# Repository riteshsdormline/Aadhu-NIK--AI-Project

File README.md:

# Aadhu-NIK--AI-Project
1. Schematic and PCB Design
   consisting of Scheamtic Diagram and PCB Design for used components(Designed on KiCAD)

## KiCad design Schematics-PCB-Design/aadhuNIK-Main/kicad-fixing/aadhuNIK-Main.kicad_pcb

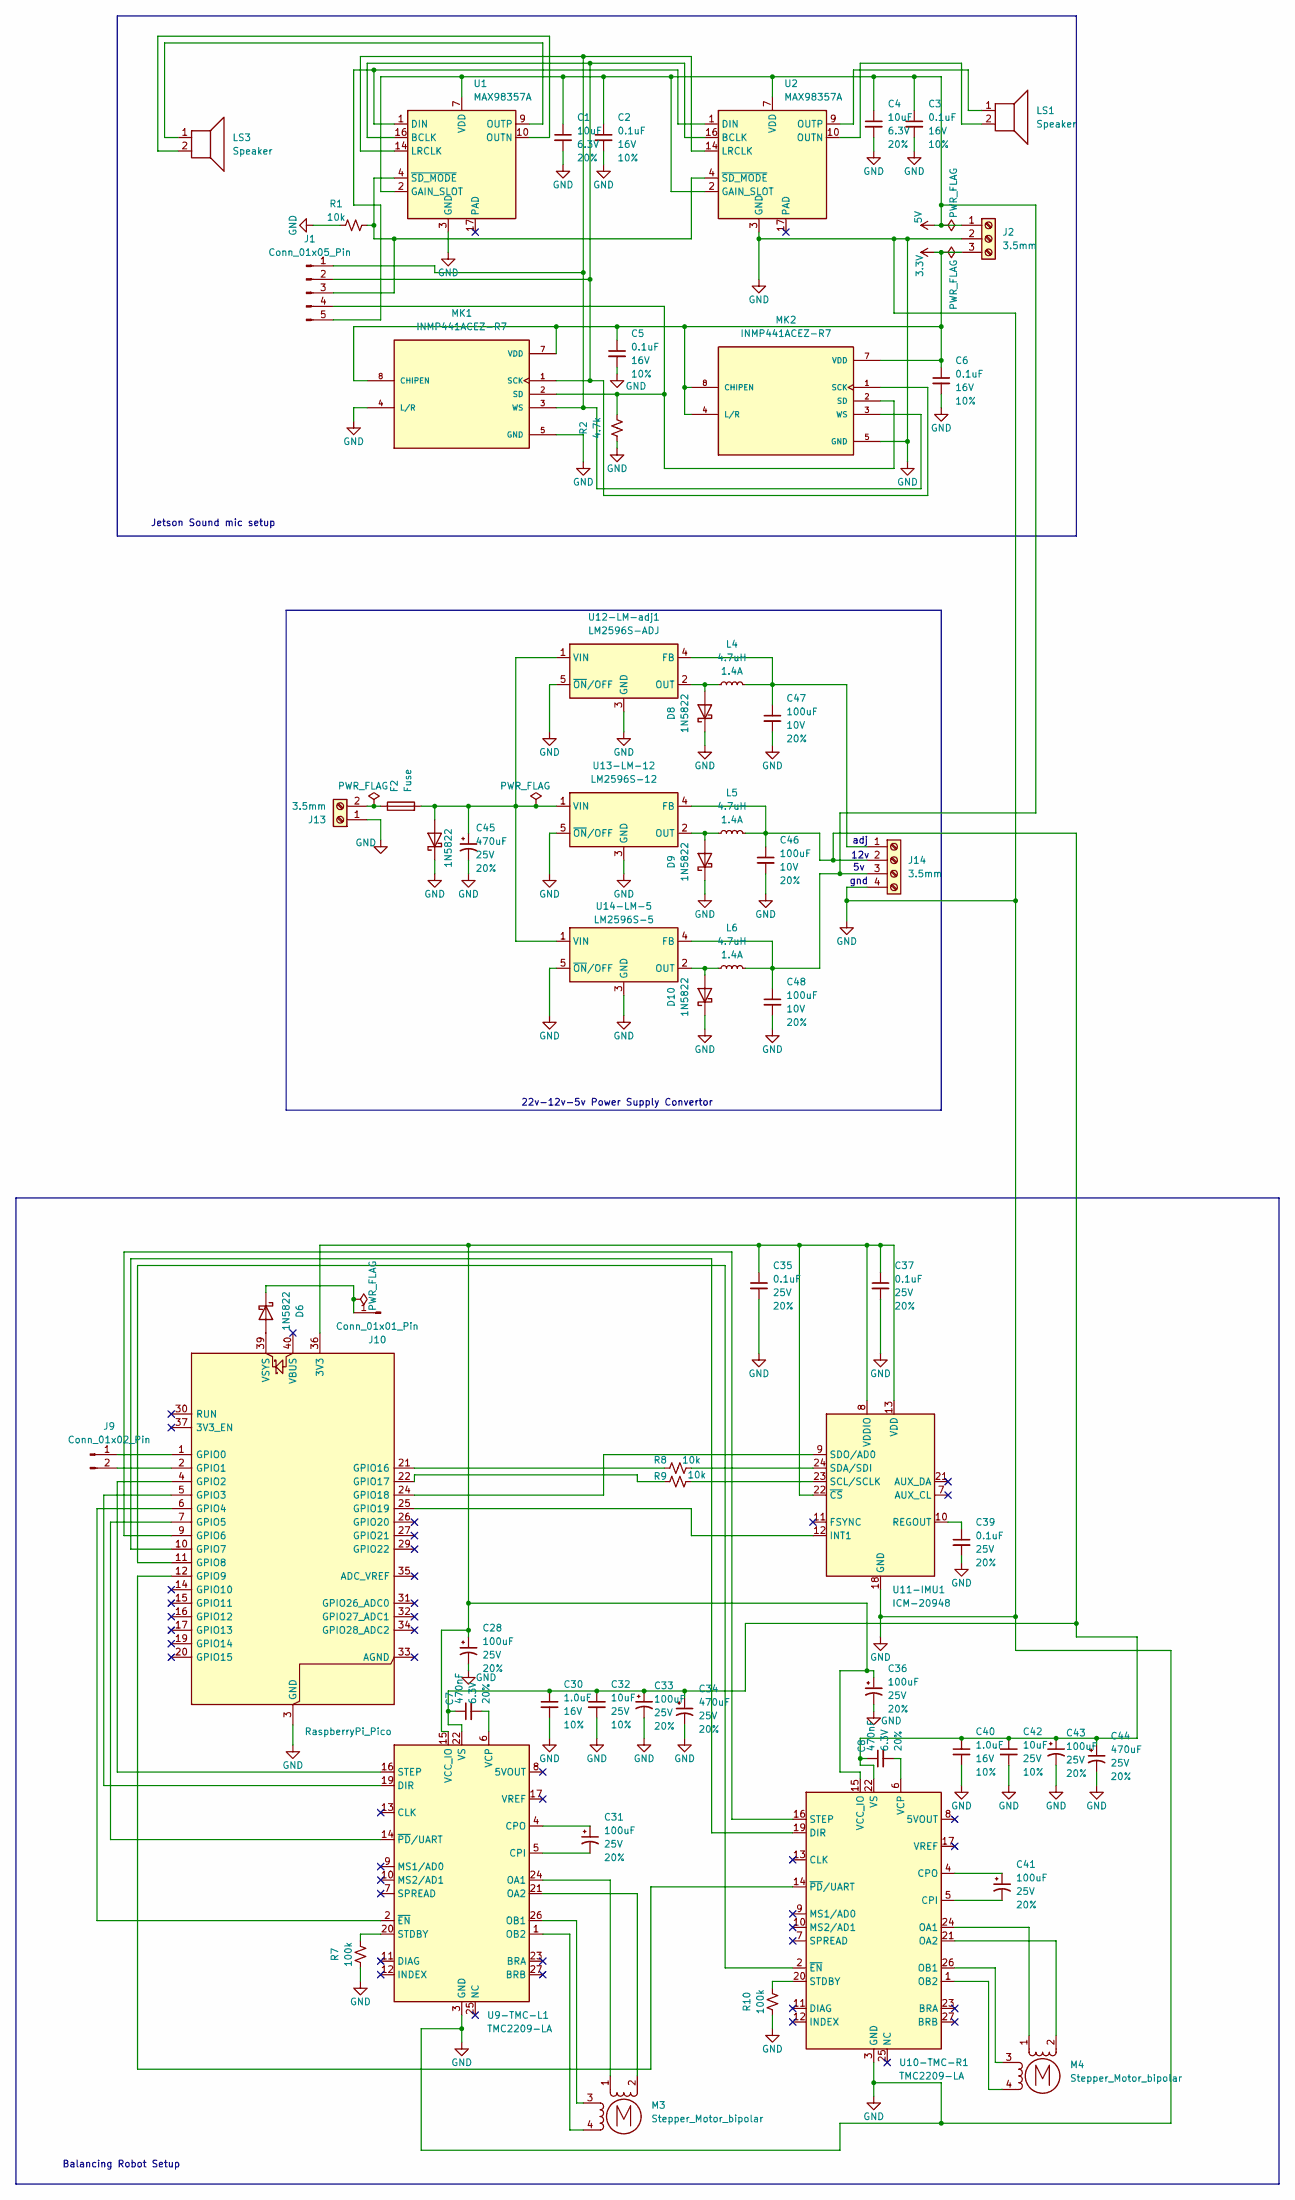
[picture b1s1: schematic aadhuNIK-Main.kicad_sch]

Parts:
A2: RaspberryPi_Pico; RaspberryPi_Pico_Common_Unspecified
C1, C4: 10uF; C_0402_1005Metric; Voltage 6.3V; Tolerance 20%
C2: 0.1uF; C_01005_0402Metric; Voltage 16V; Tolerance 10%
C3, C5, C6: 0.1uF; C_0402_1005Metric; Voltage 16V; Tolerance 10%
C7, C8: 470nF; C_0201_0603Metric; Voltage 6.3V; Tolerance 20%
C28, C31, C33, C36, C41, C43: 100uF; Panasonic_D; Voltage 25V; Tolerance 20%
C30, C40: 1.0uF; C_0402_1005Metric; Voltage 16V; Tolerance 10%
C32, C42: 10uF; C_0805_2012Metric; Voltage 25V; Tolerance 10%
C34, C44, C45: 470uF; Electrolytic_10.3x10.3mm; Voltage 25V; Tolerance 20%
C35, C37, C39: 0.1uF; C_0603_1608Metric; Voltage 25V; Tolerance 20%
C46, C47, C48: 100uF; C_1206_3216Metric; Voltage 10V; Tolerance 20%
D6, D7, D8, D9, D10: 1N5822; D_DO-201AD_P15.24mm_Horizontal
F2: Fuse; Fuse_0603_1608Metric
J1: Conn_01x05_Pin; Hirose_DF13-05P-1.25DSA_1x05_P1.25mm_Vertical
J2: 3.5mm; ScrewTerminal_1x03_P3.5mm_Horizontal_Black
J9: Conn_01x02_Pin; JWT_A3963_1x02_P3.96mm_Vertical
J10: Conn_01x01_Pin; Hirose_DF63M-1P-3.96DSA_1x01_P3.96mm_Vertical
J13: 3.5mm; ScrewTerminal_1x02_P3.5mm_Horizontal_Black
J14: 3.5mm; ScrewTerminal_1x04_P3.5mm_Horizontal
L4, L5, L6: 4.7uH; 1008_2520Metric
LS1, LS3: Speaker; JWT_A3963_1x02_P3.96mm_Vertical
M3, M4: Stepper_Motor_bipolar; PinHeader_1x04_P2.54mm_Vertical
MK1, MK2: INMP441ACEZ-R7; MIC_INMP441ACEZ-R7; PARTREV 1.1
R1: 10k; R_0402_1005Metric
R2: 4.7k; R_0402_1005Metric
R7, R10: 100k; R_0603_1608Metric
R8, R9: 10k; R_0603_1608Metric
U1: MAX98357A; TQFN-16-1EP_3x3mm_P0.5mm_EP1.23x1.23mm_ThermalVias
U2: MAX98357A; TQFN-16-1EP_3x3mm_P0.5mm_EP1.23x1.23mm
U9-TMC-L1, U10-TMC-R1: TMC2209-LA; VQFN-28-1EP_5x5mm_P0.5mm_EP3.7x3.7mm_ThermalVias
U11-IMU1: ICM-20948; InvenSense_QFN-24_3x3mm_P0.4mm
U12-LM-adj1: LM2596S-ADJ; TO-263-5_TabPin3
U13-LM-12: LM2596S-12; TO-263-5_TabPin3
U14-LM-5: LM2596S-5; TO-263-5_TabPin3

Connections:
3.3V: C5.1, C6.1, J2.3, MK1.7 (VDD), MK1.8 (CHIPEN), MK2.4 (L/R), MK2.7 (VDD), MK2.8 (CHIPEN)
5V: C1.1, C2.1, C3.1, C4.1, C48.1, J2.1, J14.3, L6.2, U1.2 (GAIN_SLOT), U1.7 (VDD), U1.8 (VDD), U2.2 (GAIN_SLOT), U2.7 (VDD), U2.8 (VDD), U14-LM-5.4 (FB)
GND: A2.3 (GND), A2.8 (GND), A2.13 (GND), A2.18 (GND), A2.23 (GND), A2.28 (GND), A2.38 (GND), C1.2, C2.2, C3.2, C4.2, C5.2, C6.2, C28.2, C30.2, C32.2, C33.2, C34.2, C35.2, C36.2, C37.2, C39.2, C40.2, C42.2, C43.2, C44.2, C45.2, C46.2, C47.2, C48.2, D7.1 (K), D8.1 (K), D9.1 (K), D10.1 (K), J2.2, J13.1, J14.4, MK1.4 (L/R), MK1.5 (GND), MK1.6 (GND), MK1.9 (GND), MK2.5 (GND), MK2.6 (GND), MK2.9 (GND), R1.1, R2.1, R7.1, R10.1, U1.3 (GND), U1.11 (GND), U1.15 (GND), U2.3 (GND), U2.11 (GND), U2.15 (GND), U9-TMC-L1.3 (GND), U9-TMC-L1.18 (GND), U9-TMC-L1.29 (GND), U10-TMC-R1.3 (GND), U10-TMC-R1.18 (GND), U10-TMC-R1.29 (GND), U11-IMU1.18 (GND), U11-IMU1.20 (GND), U12-LM-adj1.3 (GND), U12-LM-adj1.5 (~ON/OFF), U13-LM-12.3 (GND), U13-LM-12.5 (~ON/OFF), U14-LM-5.3 (GND), U14-LM-5.5 (~ON/OFF)
unnamed: A2.36 (3V3), C28.1, C35.1, C36.1, C37.1, U9-TMC-L1.15 (VCC_IO), U10-TMC-R1.15 (VCC_IO), U11-IMU1.8 (VDDIO), U11-IMU1.13 (VDD), U11-IMU1.22 (~CS)
unnamed: A2.1 (GPIO0), J9.1
unnamed: A2.2 (GPIO1), J9.2
unnamed: A2.4 (GPIO2), U9-TMC-L1.16 (STEP)
unnamed: A2.5 (GPIO3), U9-TMC-L1.19 (DIR)
unnamed: A2.6 (GPIO4), U9-TMC-L1.2 (~EN)
unnamed: A2.7 (GPIO5), U9-TMC-L1.14 (~PD/UART)
unnamed: A2.9 (GPIO6), U10-TMC-R1.16 (STEP)
unnamed: A2.10 (GPIO7), U10-TMC-R1.19 (DIR)
unnamed: A2.11 (GPIO8), U10-TMC-R1.2 (~EN)
unnamed: A2.12 (GPIO9), U10-TMC-R1.14 (~PD/UART)
unnamed: A2.21 (GPIO16), R8.1
unnamed: A2.22 (GPIO17), R9.1
unnamed: A2.24 (GPIO18), U11-IMU1.9 (SDO/AD0)
unnamed: A2.25 (GPIO19), U11-IMU1.12 (INT1)
unnamed: A2.39 (VSYS), D6.2 (A)
unnamed: D6.1 (K), J10.1 (Pin_1_1)
unnamed: C45.1, D7.2 (A), F2.2, U12-LM-adj1.1 (VIN), U13-LM-12.1 (VIN), U14-LM-5.1 (VIN)
unnamed: D8.2 (A), L4.1, U12-LM-adj1.2 (OUT)
unnamed: D9.2 (A), L5.1, U13-LM-12.2 (OUT)
unnamed: D10.2 (A), L6.1, U14-LM-5.2 (OUT)
unnamed: J1.1, MK1.3 (WS), MK2.3 (WS), U1.14 (LRCLK), U2.14 (LRCLK)
unnamed: J1.2, MK1.1 (SCK), MK2.1 (SCK), U1.16 (BCLK), U2.16 (BCLK)
unnamed: J1.3, R1.2, U1.4 (~SD_MODE), U2.4 (~SD_MODE)
unnamed: J1.4, MK1.2 (SD), MK2.2 (SD), R2.2
unnamed: J1.5, U1.1 (DIN), U2.1 (DIN)
unnamed: F2.1, J13.2
unnamed: C47.1, J14.1, L4.2, U12-LM-adj1.4 (FB)
unnamed: C7.1, C8.1, C30.1, C32.1, C33.1, C34.1, C40.1, C42.1, C43.1, C44.1, C46.1, J14.2, L5.2, U9-TMC-L1.22 (VS), U9-TMC-L1.28 (VS), U10-TMC-R1.22 (VS), U10-TMC-R1.28 (VS), U13-LM-12.4 (FB)
unnamed: M3.2 (-_2), U9-TMC-L1.21 (OA2)
unnamed: M4.2 (-_2), U10-TMC-R1.21 (OA2)
unnamed: LS3.2, U1.10 (OUTN)
unnamed: LS3.1, U1.9 (OUTP)
unnamed: LS1.2, U2.10 (OUTN)
unnamed: LS1.1, U2.9 (OUTP)
unnamed: C31.2, U9-TMC-L1.5 (CPI)
unnamed: C31.1, U9-TMC-L1.4 (CPO)
unnamed: M3.1, U9-TMC-L1.24 (OA1)
unnamed: M3.3, U9-TMC-L1.26 (OB1)
unnamed: M3.4, U9-TMC-L1.1 (OB2)
unnamed: R7.2, U9-TMC-L1.20 (STDBY)
unnamed: C7.2, U9-TMC-L1.6 (VCP)
unnamed: C41.2, U10-TMC-R1.5 (CPI)
unnamed: C41.1, U10-TMC-R1.4 (CPO)
unnamed: M4.1, U10-TMC-R1.24 (OA1)
unnamed: M4.3, U10-TMC-R1.26 (OB1)
unnamed: M4.4, U10-TMC-R1.1 (OB2)
unnamed: R10.2, U10-TMC-R1.20 (STDBY)
unnamed: C8.2, U10-TMC-R1.6 (VCP)
unnamed: C39.1, U11-IMU1.10 (REGOUT)
unnamed: R9.2, U11-IMU1.23 (SCL/SCLK)
unnamed: R8.2, U11-IMU1.24 (SDA/SDI)

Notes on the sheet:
Balancing Robot Setup
12v
adj
Jetson Sound mic setup
gnd
22v-12v-5v Power Supply Convertor

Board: 2 copper layers, 63 parts (0 on the bottom side), 55 nets, no tracks yet.

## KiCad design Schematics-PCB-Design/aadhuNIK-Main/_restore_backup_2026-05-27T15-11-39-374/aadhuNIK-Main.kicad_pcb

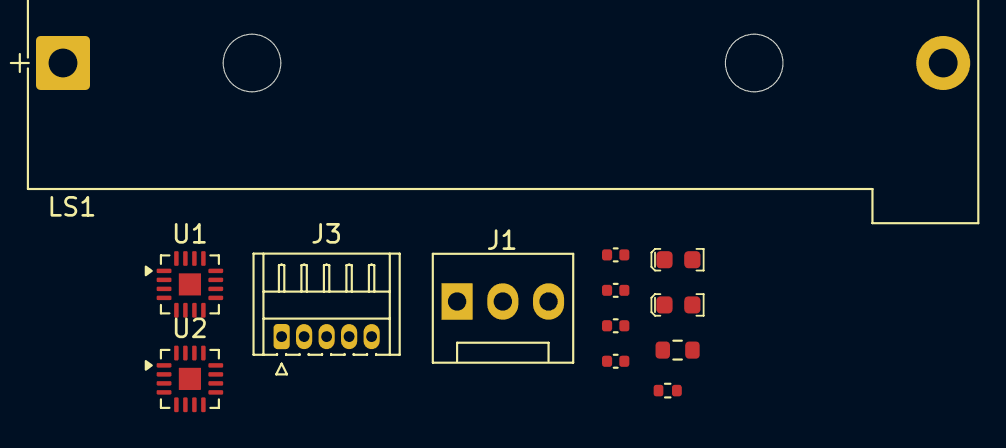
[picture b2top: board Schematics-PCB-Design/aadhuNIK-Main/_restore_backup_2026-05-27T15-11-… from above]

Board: 2 copper layers, 13 parts (0 on the bottom side), 11 nets, no tracks yet.

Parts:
C1, C2, C4, C6: 0.1uF; C_0402_1005Metric
C3, C5: 10uF; C_0603_1608Metric_Polar
J1: Conn_01x03_Pin; FanPinHeader_1x03_P2.54mm_Vertical
J3: Conn_01x05_Pin; Hirose_DF13-05P-1.25DS_1x05_P1.25mm_Horizontal
LS1: Speaker; BatteryHolder_Bulgin_BX0034_1xAAA
R1: 100k; R_0402_1005Metric
R2: 4.7k; R_0603_1608Metric
U1, U2: MAX98357A; TQFN-16-1EP_3x3mm_P0.5mm_EP1.23x1.23mm

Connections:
GND: C1.2, C2.2, C3.2, C4.2, C5.2, C6.2, J1.1, R1.1, U1.3 (GND), U1.11 (GND), U1.15 (GND), U2.3 (GND), U2.11 (GND), U2.15 (GND)
unnamed: C3.1, C4.1, C5.1, C6.1, J1.2, U1.2 (GAIN_SLOT), U1.7 (VDD), U1.8 (VDD), U2.2 (GAIN_SLOT), U2.7 (VDD), U2.8 (VDD)
unnamed: C1.1, C2.1, J1.3
unnamed: J3.1, U1.16 (BCLK), U2.16 (BCLK)
unnamed: J3.2, R1.2
unnamed: J3.3, U1.14 (LRCLK), U2.14 (LRCLK)
unnamed: J3.4, U1.1 (DIN), U2.1 (DIN)
unnamed: J3.5, R2.1
unnamed: LS1.2, U1.10 (OUTN)
unnamed: LS1.1, U1.9 (OUTP)
unnamed: R2.2, U1.4 (~SD_MODE), U2.4 (~SD_MODE)

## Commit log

2026-05-26 updated Schematic design almost zero errors - next pcb update
2026-05-26 Upload PCB project with clean structure
2026-05-26 Add Schematic and PCB Design section to README
    Added a section for Schematic and PCB Design details.
2026-06-01 Update KiCad schematic and PCB
